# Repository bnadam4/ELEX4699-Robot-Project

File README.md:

Github Repository for the ELEX 4699 Pi Robot Project

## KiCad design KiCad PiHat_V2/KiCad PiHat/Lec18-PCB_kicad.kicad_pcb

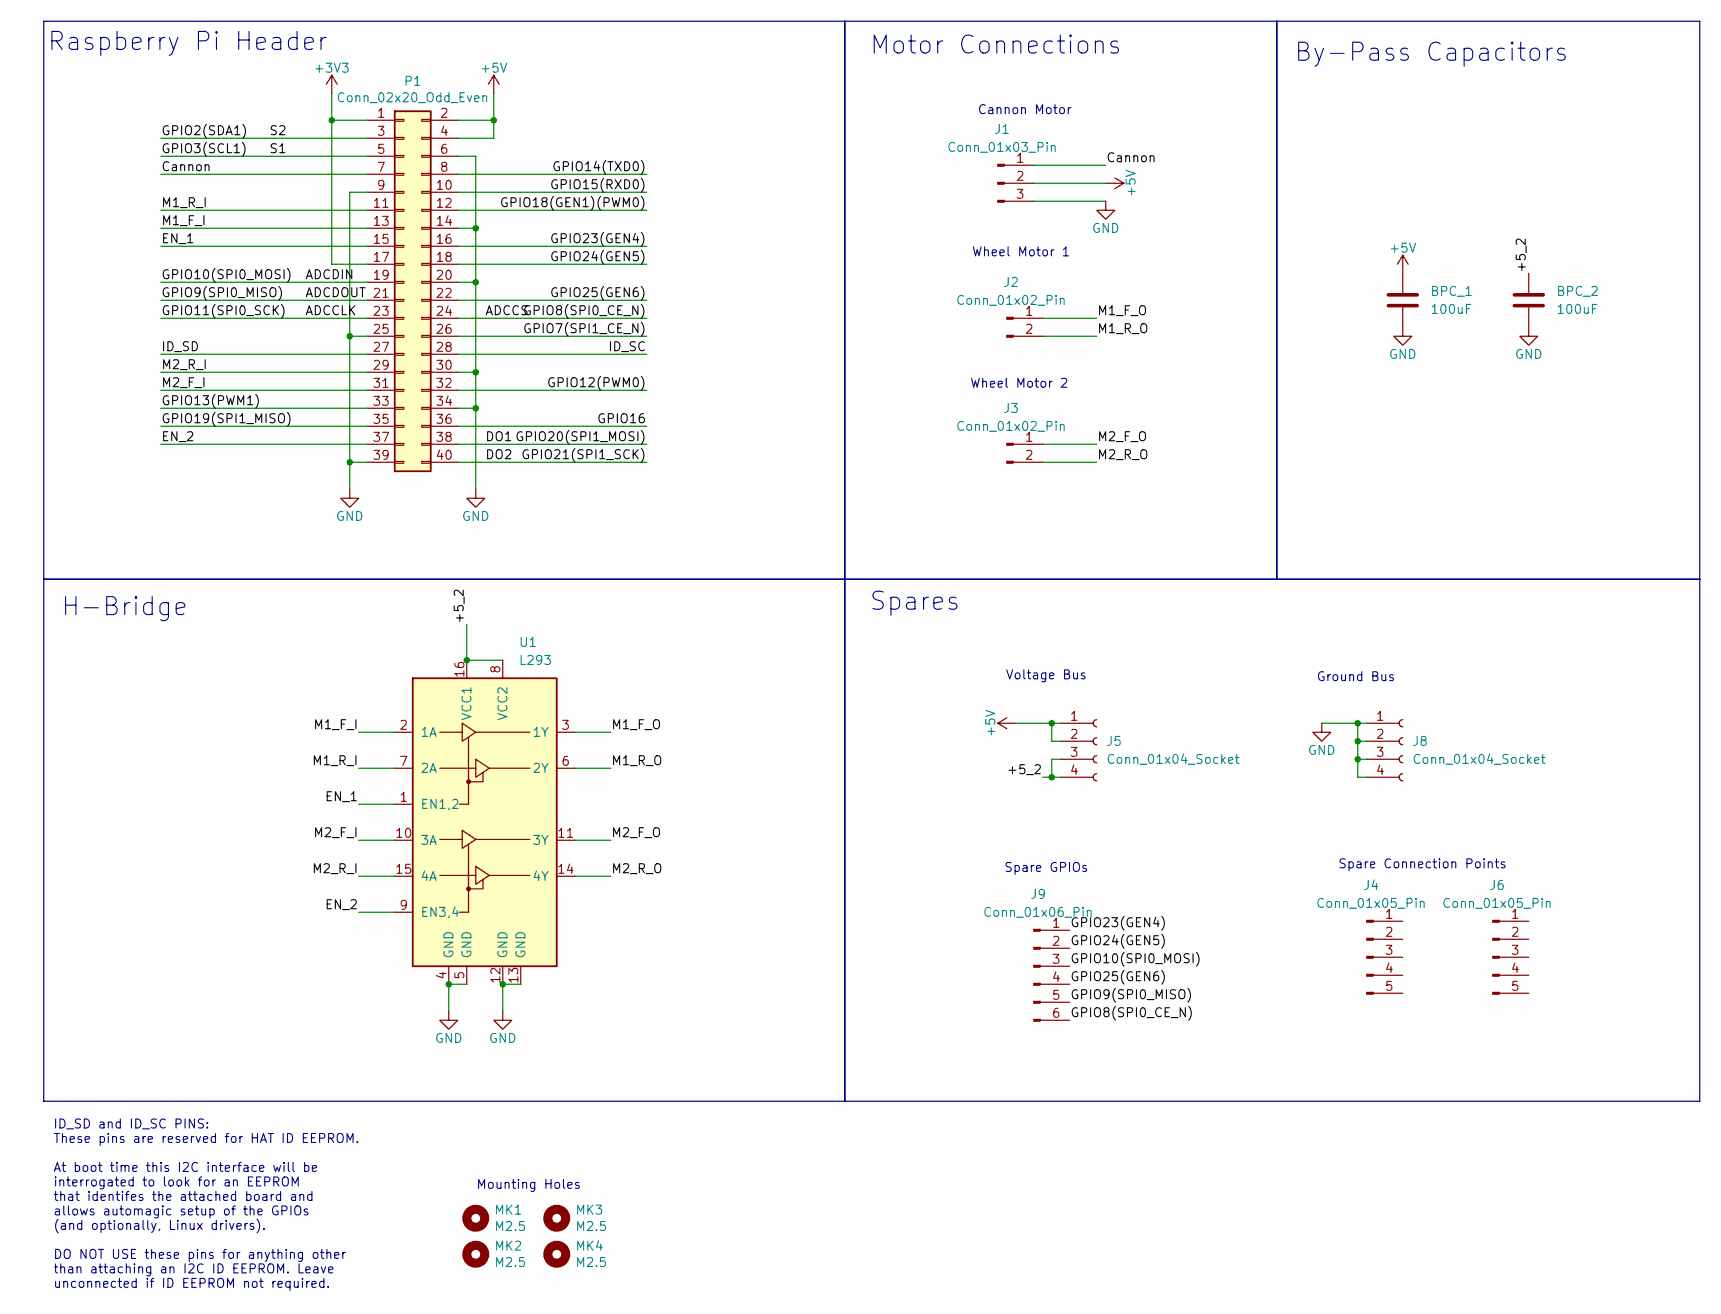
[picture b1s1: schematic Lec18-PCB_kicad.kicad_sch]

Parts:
BPC_1, BPC_2: 100uF; C_Rect_L7.0mm_W4.5mm_P5.00mm
J1: Conn_01x03_Pin; PinHeader_1x03_P2.54mm_Vertical
J2, J3: Conn_01x02_Pin; PinHeader_1x02_P2.54mm_Vertical
J4, J6: Conn_01x05_Pin; PinHeader_1x05_P2.00mm_Vertical
J5, J8: Conn_01x04_Socket; PinSocket_1x04_P2.54mm_Vertical
J9: Conn_01x06_Pin; PinHeader_1x06_P2.54mm_Vertical
MK1, MK2, MK3, MK4: M2.5; MountingHole_2.7mm_M2.5
P1: Conn_02x20_Odd_Even; PinSocket_2x20_P2.54mm_Vertical
U1: L293; DIP-16_W7.62mm

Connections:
+3V3: P1.1, P1.17
+5V: BPC_1.1, J1.2, J5.1, J5.2, P1.2, P1.4
/+5_2: BPC_2.1, J5.3, J5.4, U1.8 (VCC2), U1.16 (VCC1)
/ADCCLK: P1.23
/ADCCS: J9.6, P1.24
/ADCDIN: J9.3, P1.19
/ADCDOUT: J9.5, P1.21
/Cannon: J1.1, P1.7
/DO1: P1.38
/DO2: P1.40
/EN_1: P1.15, U1.1 (EN1,2)
/EN_2: P1.37, U1.9 (EN3,4)
/GPIO2(SDA1): P1.3
/GPIO3(SCL1): P1.5
/GPIO7(SPI1_CE_N): P1.26
/GPIO12(PWM0): P1.32
/GPIO13(PWM1): P1.33
/GPIO14(TXD0): P1.8
/GPIO15(RXD0): P1.10
/GPIO16: P1.36
/GPIO18(GEN1)(PWM0): P1.12
/GPIO19(SPI1_MISO): P1.35
/GPIO23(GEN4): J9.1, P1.16
/GPIO24(GEN5): J9.2, P1.18
/GPIO25(GEN6): J9.4, P1.22
/ID_SC: P1.28
/ID_SD: P1.27
/M1_F_I: P1.13, U1.2 (1A)
/M1_F_O: J2.1, U1.3 (1Y)
/M1_R_I: P1.11, U1.7 (2A)
/M1_R_O: J2.2, U1.6 (2Y)
/M2_F_I: P1.31, U1.10 (3A)
/M2_F_O: J3.1, U1.11 (3Y)
/M2_R_I: P1.29, U1.15 (4A)
/M2_R_O: J3.2, U1.14 (4Y)
GND: BPC_1.2, BPC_2.2, J1.3, J8.1, J8.2, J8.3, J8.4, P1.6, P1.9, P1.14, P1.20, P1.25, P1.30, P1.34, P1.39, U1.4 (GND), U1.5 (GND), U1.12 (GND), U1.13 (GND)

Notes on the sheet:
Motor Connections
Spares
Ground Bus
Voltage Bus
Spare GPIOs
ID_SD and ID_SC PINS: These pins are reserved for HAT ID EEPROM. At boot time this I2C interface will be interrogated to look for an EEPROM that identifes the attached board and allows automagic setup of the GPIOs (and optionally, Linux drivers). DO NOT USE these pins for anything other than attach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
Spare Connection Points
Wheel Motor 1
Wheel Motor 2
H-Bridge
By-Pass Capacitors
Cannon Motor
Raspberry Pi Header
Mounting Holes

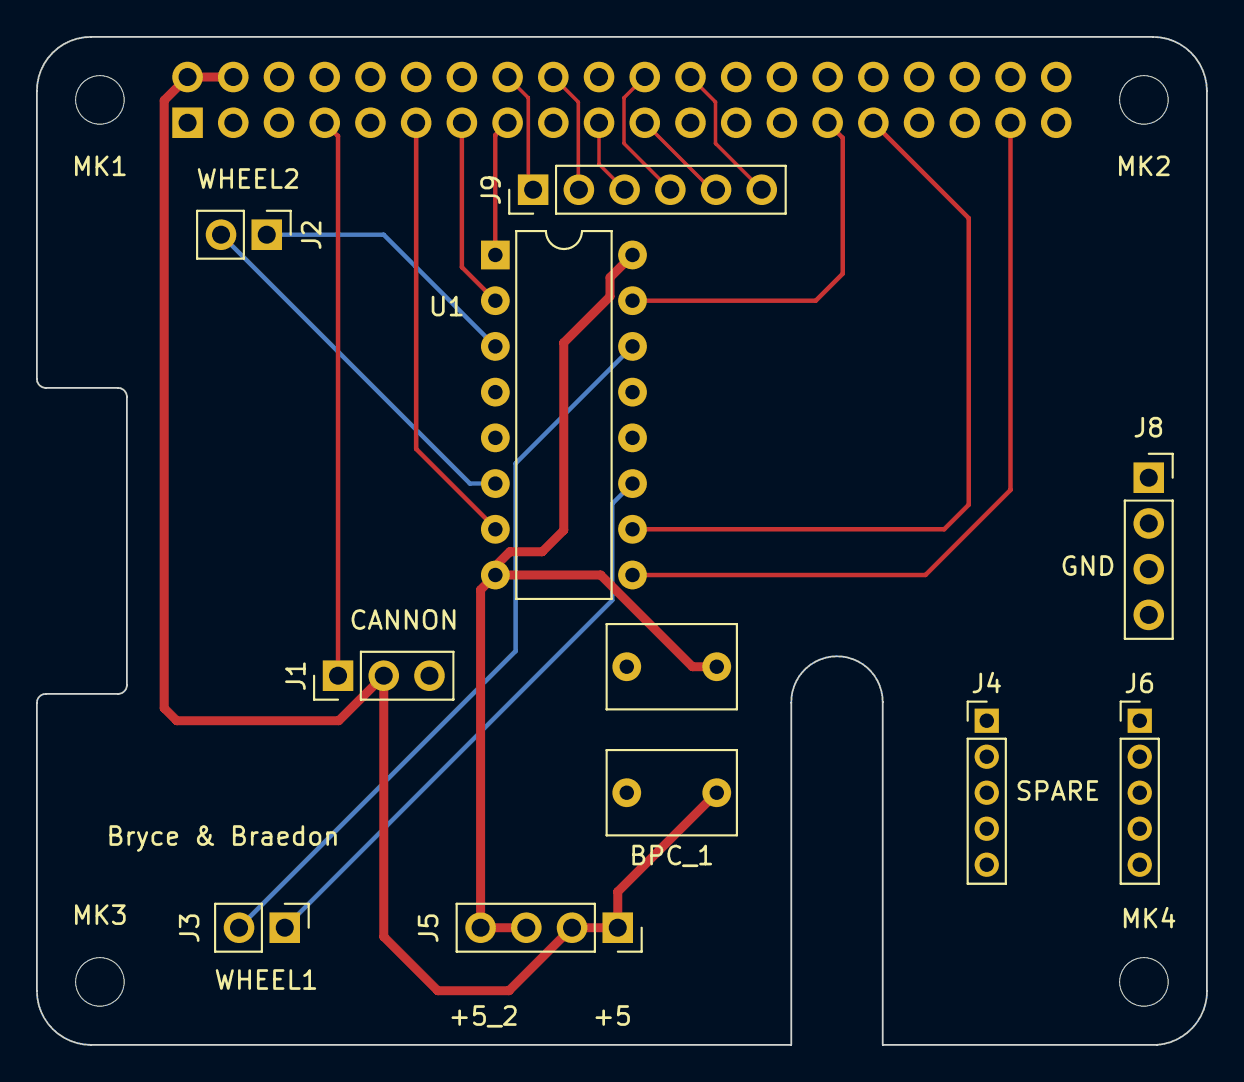
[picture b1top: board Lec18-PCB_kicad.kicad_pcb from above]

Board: 2 copper layers, 65.0 x 56.0 mm, 16 parts (1 on the bottom side), 21 nets.

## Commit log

2024-04-22 Added Car.h top level file
2024-04-22 test
2024-04-23 Established basic client-server communicaiton
2024-04-23 Car motor control and pin designations
2024-04-25 Car can now complete milestone 1
2024-04-27 Added client and added aruco detection to Pi code
2024-04-27 Added fire and turn cannon fuctions in CCar, added logic in main for firing and turning cannon, archived old CCar
2024-04-28 Attempting to get image transmission working. Still no success
2024-04-30 Successfully got communication working
2024-05-10 Final version on of code. Capable of completing the arena autonomously
